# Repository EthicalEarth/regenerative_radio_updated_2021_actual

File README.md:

# regenerative_radio_updated_2021
A new hight-sensitive regenerative radio receiver with electronical control (varicap).

Radio is receiving signals in the range of 20-40 meters. 
The frequency range depends on the specifically installed components that were measured during operation. The coil was used with 30-40 turns on a diameter of 20 mm, and a varicap is being used with 20...500 pF capacity.

The sound and receiving quality was increaced, and better than first project https://github.com/EthicalEarth/superregenerative_radio_2019_actual

ONLY AM Mode, SSB wasn't tested

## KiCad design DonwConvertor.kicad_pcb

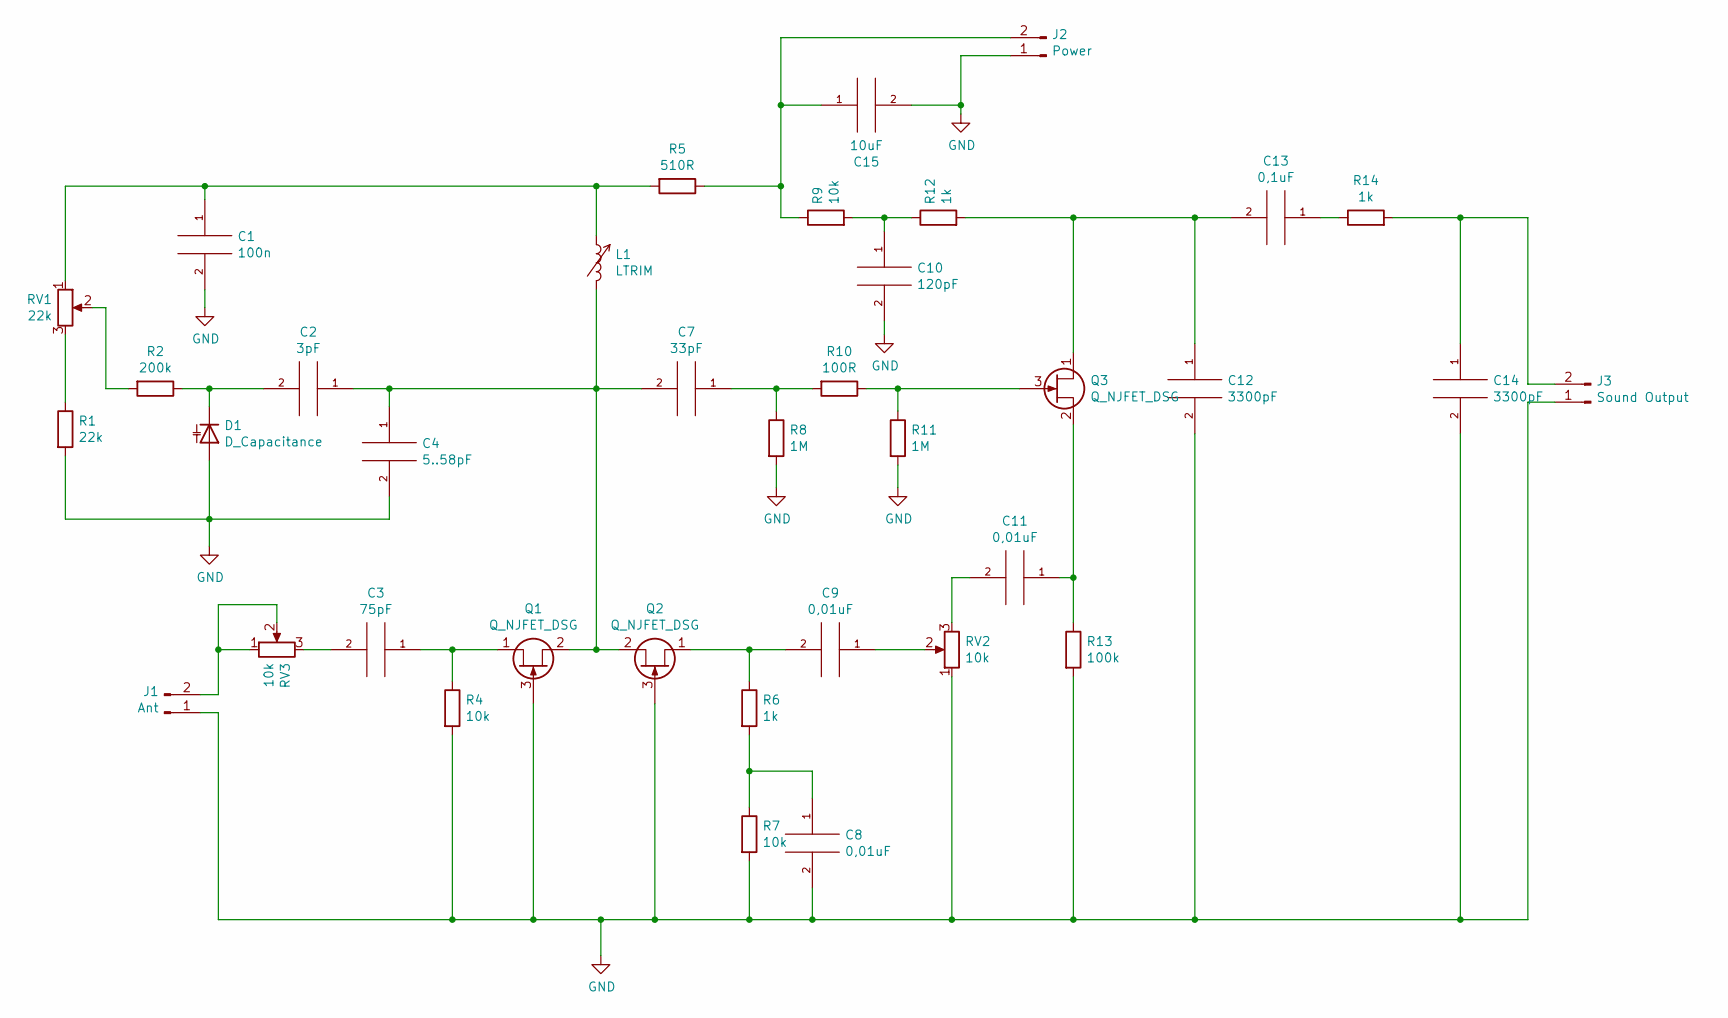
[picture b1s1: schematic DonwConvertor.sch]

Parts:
C1: 100n; C_Axial_L3.8mm_D2.6mm_P7.50mm_Horizontal
C2: 3pF; CP_Radial_Tantal_D4.5mm_P5.00mm
C3: 75pF; C_Disc_D4.3mm_W1.9mm_P5.00mm
C4: 5..58pF; C_Axial_L3.8mm_D2.6mm_P7.50mm_Horizontal
C7: 33pF; C_Disc_D4.3mm_W1.9mm_P5.00mm
C8, C9, C11: 0,01uF; C_Axial_L3.8mm_D2.6mm_P7.50mm_Horizontal
C10: 120pF; C_Disc_D4.3mm_W1.9mm_P5.00mm
C12, C14: 3300pF; C_Axial_L3.8mm_D2.6mm_P7.50mm_Horizontal
C13: 0,1uF; C_Axial_L3.8mm_D2.6mm_P7.50mm_Horizontal
C15: 10uF; CP_Axial_L10.0mm_D4.5mm_P15.00mm_Horizontal
D1: D_Capacitance; D_A-405_P10.16mm_Horizontal
J1: Ant; PinHeader_1x02_P2.54mm_Vertical
J2: Power; PinHeader_1x02_P2.54mm_Vertical
J3: Sound Output; PinHeader_1x02_P2.54mm_Vertical
L1: LTRIM; L_Axial_L16.0mm_D7.5mm_P20.32mm_Horizontal_Fastron_XHBCC
Q1, Q2, Q3: Q_NJFET_DSG; TO-92S_Wide
R1: 22k; R_Axial_DIN0207_L6.3mm_D2.5mm_P7.62mm_Horizontal
R2: 200k; R_Axial_DIN0207_L6.3mm_D2.5mm_P7.62mm_Horizontal
R4, R7, R9: 10k; R_Axial_DIN0207_L6.3mm_D2.5mm_P7.62mm_Horizontal
R5: 510R; R_Axial_DIN0207_L6.3mm_D2.5mm_P7.62mm_Horizontal
R6, R12, R14: 1k; R_Axial_DIN0207_L6.3mm_D2.5mm_P7.62mm_Horizontal
R8, R11: 1M; R_Axial_DIN0207_L6.3mm_D2.5mm_P7.62mm_Horizontal
R10: 100R; R_Axial_DIN0207_L6.3mm_D2.5mm_P7.62mm_Horizontal
R13: 100k; R_Axial_DIN0207_L6.3mm_D2.5mm_P7.62mm_Horizontal
RV1: 22k; Potentiometer_Bourns_3386C_Horizontal
RV2, RV3: 10k; Potentiometer_Bourns_3386C_Horizontal

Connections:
GND: C1.2, C4.2, C8.2, C10.2, C12.2, C14.2, C15.2, D1.2 (A), J1.1, J2.1, J3.1, Q1.3 (G), Q2.3 (G), R1.2, R4.2, R7.2, R8.2, R11.2, R13.2, RV2.1
unnamed: C1.1, L1.1, R5.2, RV1.1
unnamed: C2.1, C4.1, C7.2, L1.2, Q1.2 (S), Q2.2 (S)
unnamed: C2.2, D1.1 (K), R2.1
unnamed: C3.1, Q1.1 (D), R4.1
unnamed: C3.2, RV3.3
unnamed: C7.1, R8.1, R10.2
unnamed: C8.1, R6.2, R7.1
unnamed: C9.1, RV2.2
unnamed: C9.2, Q2.1 (D), R6.1
unnamed: C10.1, R9.2, R12.1
unnamed: C11.1, Q3.2 (S), R13.1
unnamed: C11.2, RV2.3
unnamed: C12.1, C13.2, Q3.1 (D), R12.2
unnamed: C13.1, R14.1
unnamed: C14.1, J3.2, R14.2
unnamed: C15.1, J2.2, R5.1, R9.1
unnamed: J1.2, RV3.1, RV3.2
unnamed: Q3.3 (G), R10.1, R11.1
unnamed: R1.1, RV1.3
unnamed: R2.2, RV1.2

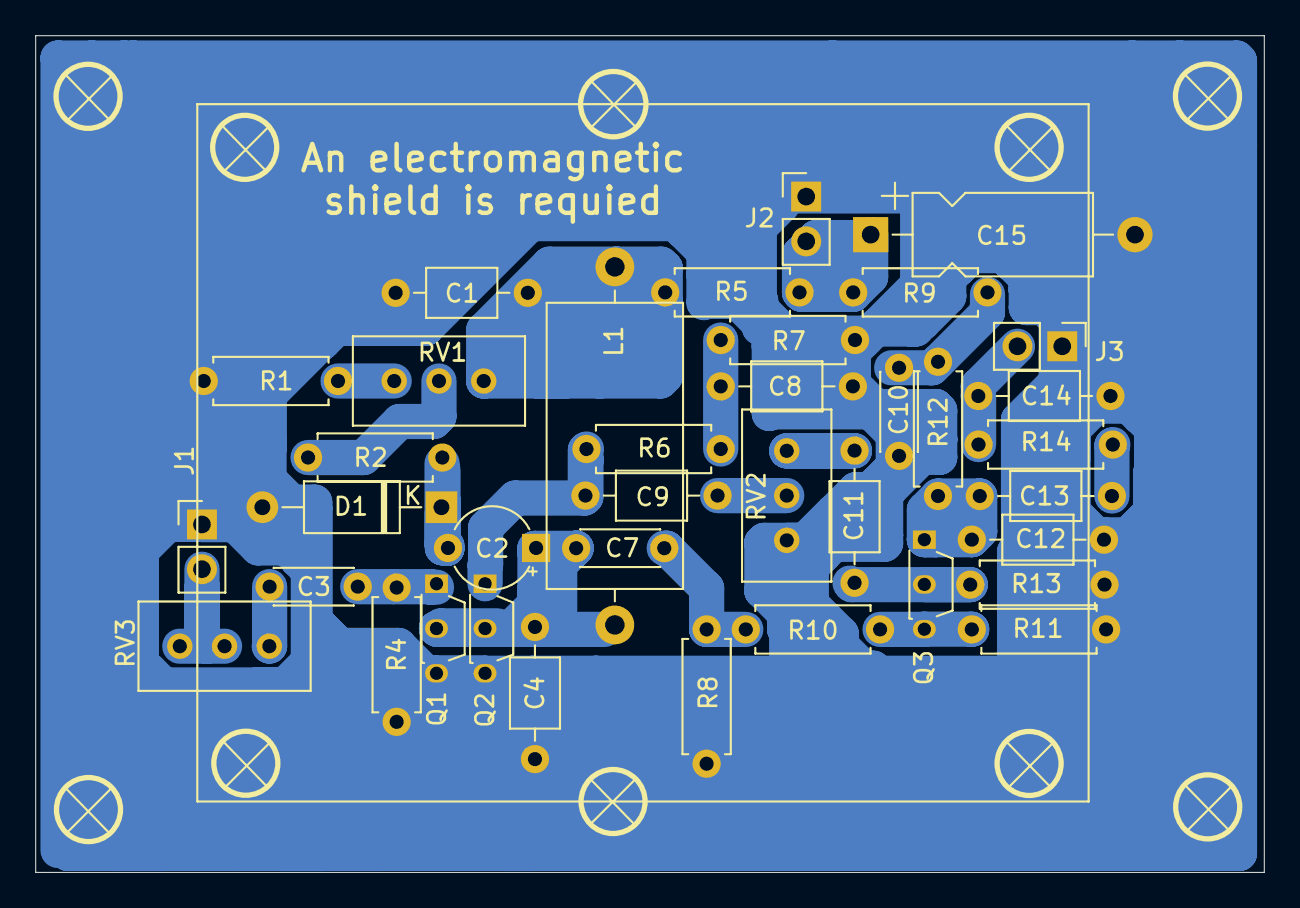
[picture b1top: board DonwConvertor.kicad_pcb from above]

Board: 2 copper layers, 69.7 x 47.5 mm, 37 parts (0 on the bottom side), 21 nets.

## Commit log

2021-08-25 First release
